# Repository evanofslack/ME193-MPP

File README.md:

# ME193-MPP
Microcontroller Programing Projects

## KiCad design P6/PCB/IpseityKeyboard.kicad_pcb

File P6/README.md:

# Ipseity Keyboard

This is a custom split keyboard PCB design. It features hotswap keyswitch support, dual rotary encoders, 64x128 OLED display, I2C communication between halves through a TRRS jack, and individually addressable LEDs support. 

Each PCB is completly reversible so that only one PCB design can be used for both the right and left halves.

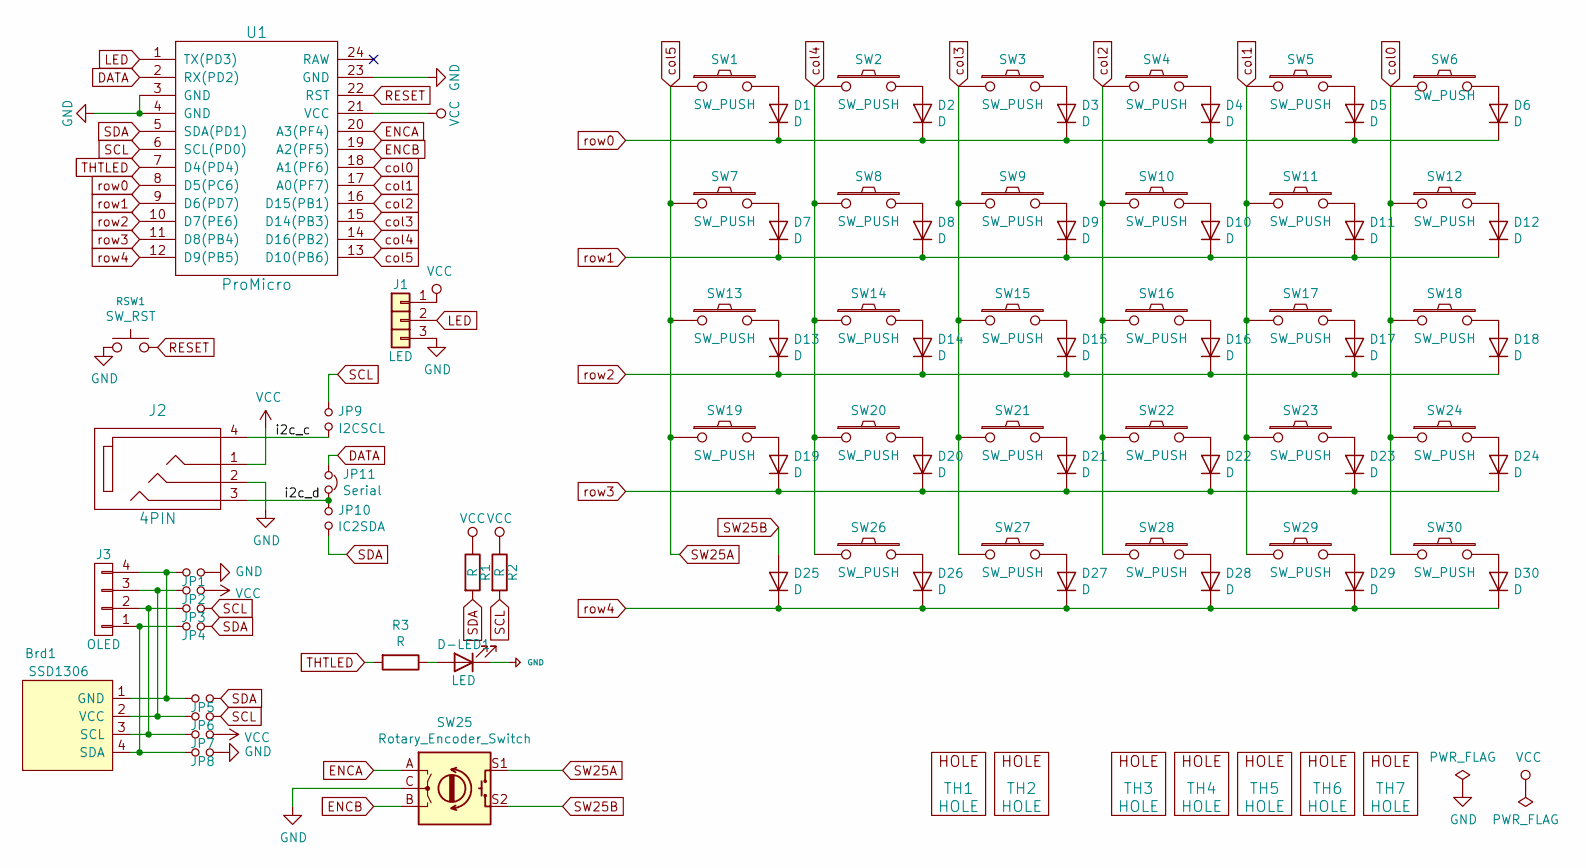
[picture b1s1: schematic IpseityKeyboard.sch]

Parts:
Brd1: SSD1306; 128x64OLED
D1, D2, D3, D4, D5, D6, D7, D8, D9, D10, D11, D12, D13, D14, D15, D16, D17, D18, D19, D20, D21, D22, D23, D24, D25, D26, D27, D28, D29, D30: D; Diode_SOD123
D-LED1: LED; LED_D3.0mm
J1: LED
J2: 4PIN; MJ-4PP-9
J3: OLED; OLED_4Pin
JP1, JP2, JP3, JP4, JP5, JP6, JP7, JP8: Jumper_NO_Small; Jumper
JP9: I2CSCL; SolderJumper-2_P1.3mm_Open_TrianglePad1.0x1.5mm
JP10: IC2SDA; SolderJumper-2_P1.3mm_Open_TrianglePad1.0x1.5mm
JP11: Serial; SolderJumper-2_P1.3mm_Bridged2Bar_Pad1.0x1.5mm
R1, R2: R; R_1206_DoubleSided
R3: R; R_Axial_DIN0207_L6.3mm_D2.5mm_P7.62mm_Horizontal
RSW1: SW_RST; TACT_SWITCH_TVBP06
SW1, SW2, SW3, SW4, SW5, SW6, SW7, SW8, SW9, SW10, SW11, SW12, SW13, SW14, SW15, SW16, SW17, SW18, SW19, SW20, SW21, SW22, SW23, SW24, SW27, SW28, SW29, SW30: SW_PUSH; CherryMX_Hotswap
SW25: Rotary_Encoder_Switch; RotaryEncoder_Alps_EC11E-Switch_Vertical_H20mm-keebio_modif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
SW26: SW_PUSH; CherryMX_Hotswap_1.5
TH1, TH2: HOLE; M2_HOLE_PCB
TH3, TH4, TH5, TH6, TH7: HOLE; HOLE_M2_TH
U1: ProMicro; ArduinoProMicro-ZigZag-DoubleSided

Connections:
/i2c_c: J2.4, JP9.2
/i2c_d: J2.3, JP10.1, JP11.2
DATA: JP11.1, U1.2 (RX(PD2))
ENCA: SW25.A, U1.20 (A3(PF4))
ENCB: SW25.B, U1.19 (A2(PF5))
LED: J1.2, U1.1 (TX(PD3))
unnamed: Brd1.1 (GND), J3.4, JP1.1, JP5.1
unnamed: Brd1.2 (VCC), J3.3, JP2.1, JP6.1
unnamed: Brd1.3 (SCL), J3.2, JP3.1, JP7.1
unnamed: Brd1.4 (SDA), J3.1, JP4.1, JP8.1
unnamed: D1.2 (A), SW1.2
unnamed: D2.2 (A), SW2.2
unnamed: D3.2 (A), SW3.2
unnamed: D4.2 (A), SW4.2
unnamed: D5.2 (A), SW5.2
unnamed: D6.2 (A), SW6.2
unnamed: D7.2 (A), SW7.2
unnamed: D8.2 (A), SW8.2
unnamed: D9.2 (A), SW9.2
unnamed: D10.2 (A), SW10.2
unnamed: D11.2 (A), SW11.2
unnamed: D12.2 (A), SW12.2
unnamed: D13.2 (A), SW13.2
unnamed: D14.2 (A), SW14.2
unnamed: D15.2 (A), SW15.2
unnamed: D16.2 (A), SW16.2
unnamed: D17.2 (A), SW17.2
unnamed: D18.2 (A), SW18.2
unnamed: D19.2 (A), SW19.2
unnamed: D20.2 (A), SW20.2
unnamed: D21.2 (A), SW21.2
unnamed: D22.2 (A), SW22.2
unnamed: D23.2 (A), SW23.2
unnamed: D24.2 (A), SW24.2
unnamed: D26.2 (A), SW26.2
unnamed: D27.2 (A), SW27.2
unnamed: D28.2 (A), SW28.2
unnamed: D29.2 (A), SW29.2
unnamed: D30.2 (A), SW30.2
unnamed: D-LED1.2 (A), R3.1
RESET: RSW1.2, U1.22 (RST)
SCL: JP3.2, JP6.2, JP9.1, R2.2, U1.6 (SCL(PD0))
SDA: JP4.2, JP5.2, JP10.2, R1.2, U1.5 (SDA(PD1))
SW25A: SW1.1, SW7.1, SW13.1, SW19.1, SW25.S1, U1.13 (D10(PB6))
SW25B: D25.2 (A), SW25.S2
THTLED: R3.2, U1.7 (D4(PD4))
VCC: J1.1, J2.1, JP2.2, JP7.2, R1.1, R2.1, U1.21 (VCC)
col0: SW6.1, SW12.1, SW18.1, SW24.1, SW30.1, U1.18 (A1(PF6))
col1: SW5.1, SW11.1, SW17.1, SW23.1, SW29.1, U1.17 (A0(PF7))
col2: SW4.1, SW10.1, SW16.1, SW22.1, SW28.1, U1.16 (D15(PB1))
col3: SW3.1, SW9.1, SW15.1, SW21.1, SW27.1, U1.15 (D14(PB3))
col4: SW2.1, SW8.1, SW14.1, SW20.1, SW26.1, U1.14 (D16(PB2))
row0: D1.1 (K), D2.1 (K), D3.1 (K), D4.1 (K), D5.1 (K), D6.1 (K), U1.8 (D5(PC6))
row1: D7.1 (K), D8.1 (K), D9.1 (K), D10.1 (K), D11.1 (K), D12.1 (K), U1.9 (D6(PD7))
row2: D13.1 (K), D14.1 (K), D15.1 (K), D16.1 (K), D17.1 (K), D18.1 (K), U1.10 (D7(PE6))
row3: D19.1 (K), D20.1 (K), D21.1 (K), D22.1 (K), D23.1 (K), D24.1 (K), U1.11 (D8(PB4))
row4: D25.1 (K), D26.1 (K), D27.1 (K), D28.1 (K), D29.1 (K), D30.1 (K), U1.12 (D9(PB5))

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
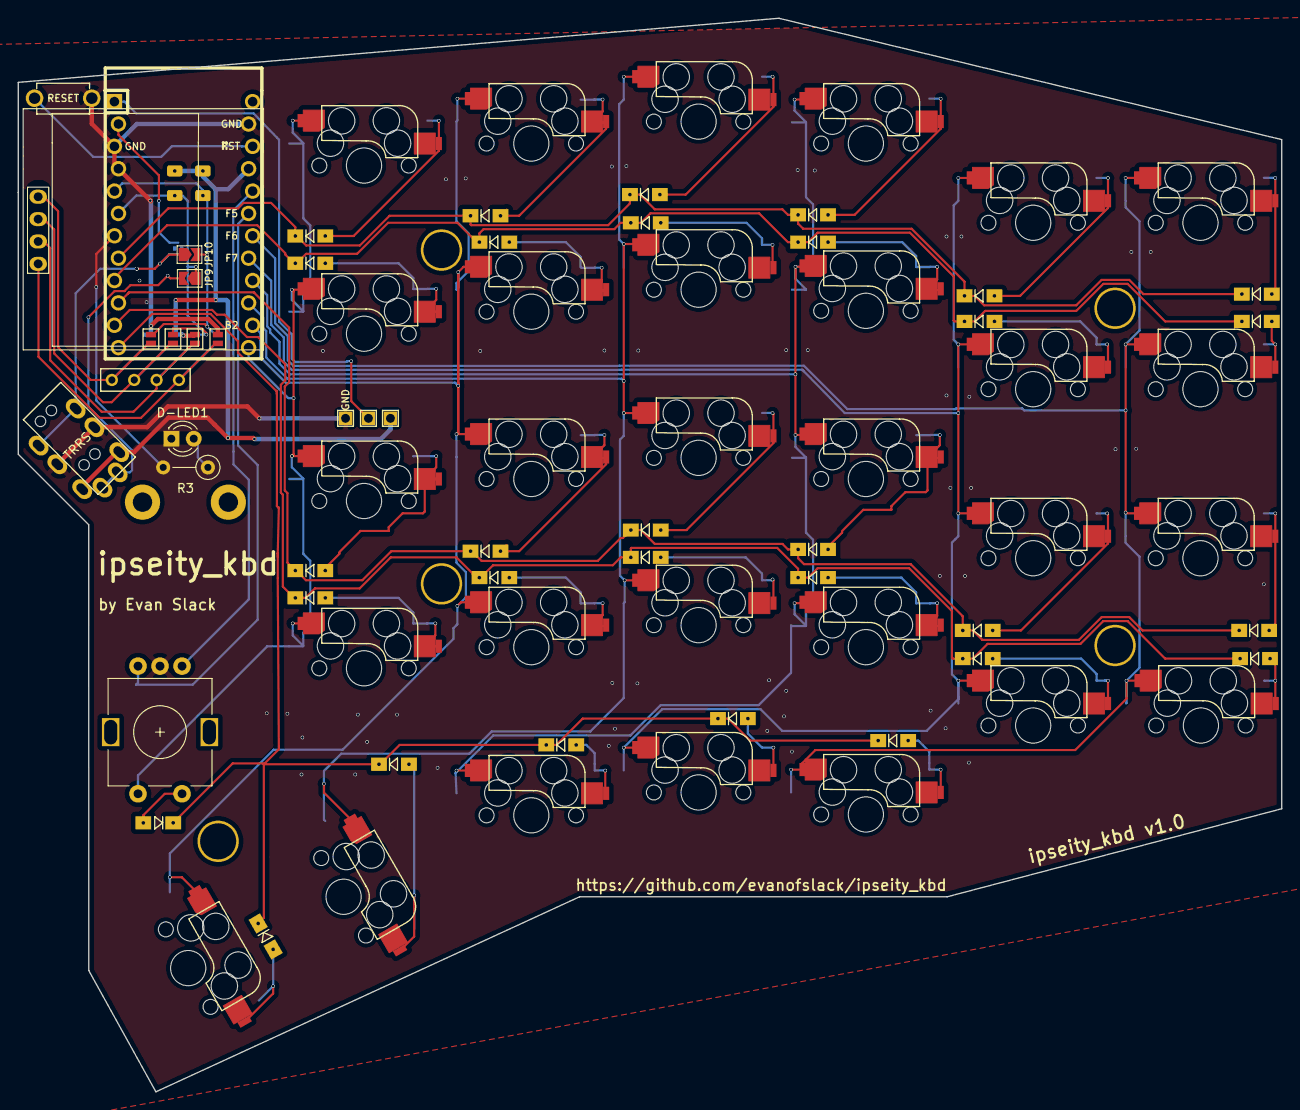
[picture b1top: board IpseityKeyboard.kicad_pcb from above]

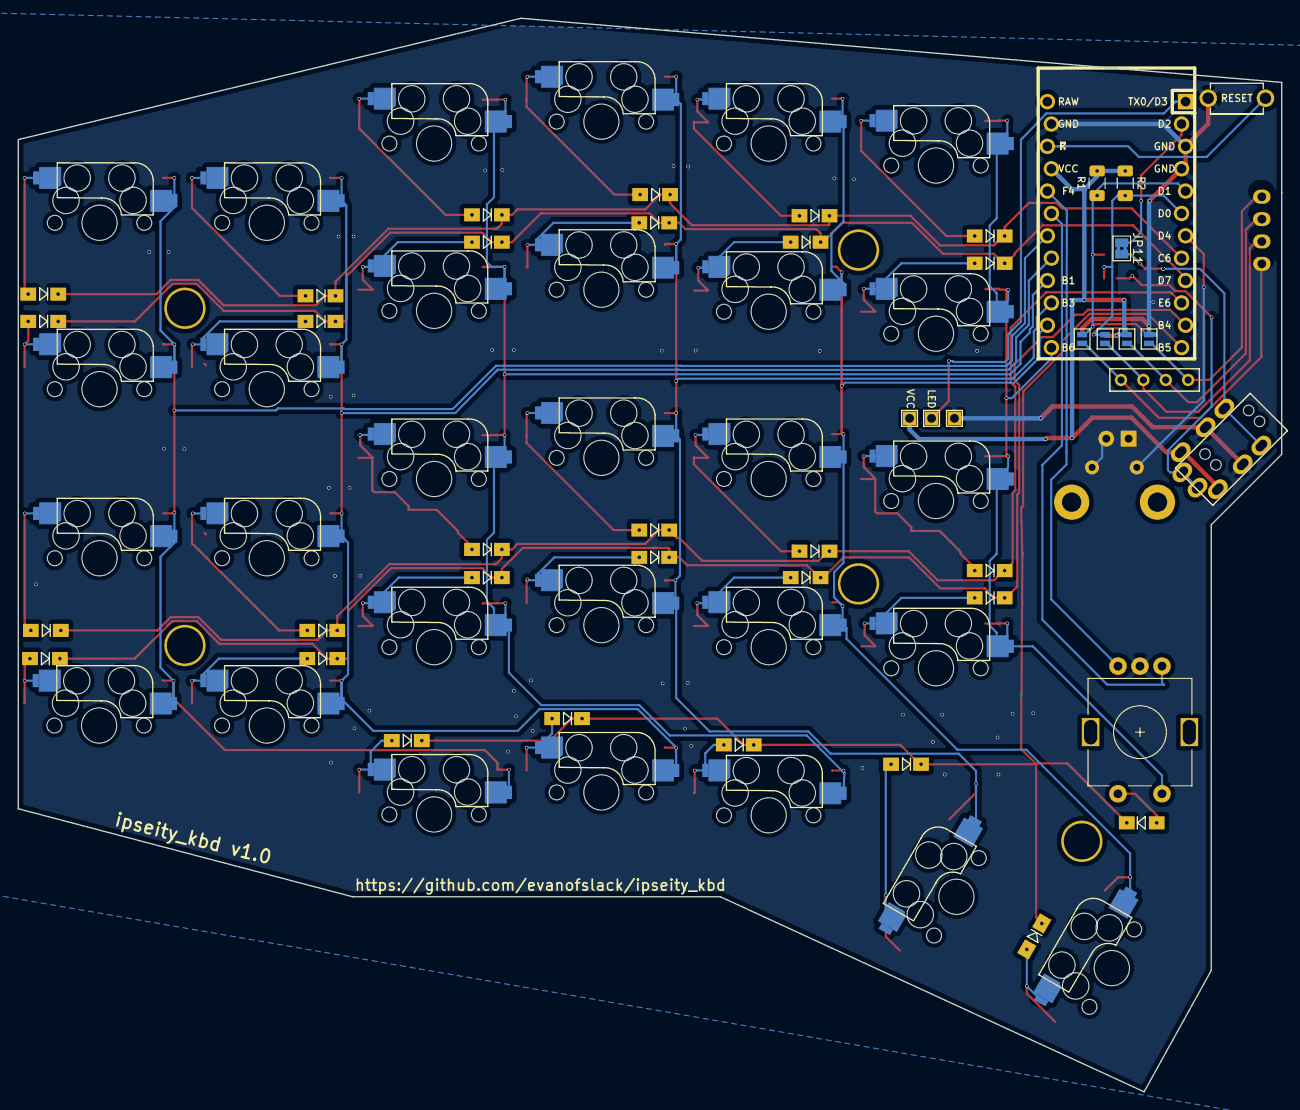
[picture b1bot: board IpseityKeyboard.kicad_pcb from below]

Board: 2 copper layers, 143.5 x 121.9 mm, 88 parts (7 on the bottom side), 58 nets.

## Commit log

2021-02-27 Added initial puzzle files
2021-03-14 Added files for P3
    Comparison of algorithms for calculating the inverse square root of a number
2021-05-12 Uploaded P5
2021-05-12 Added P6
